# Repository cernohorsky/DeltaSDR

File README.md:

# DeltaSDR
HF Software Defined Radio Transceiver that includes ADC and DAC circuits. No soundcard is needed. Board communicates only trough one USB cable. Very good software support trough Hamlib. Ideal for digital modes such a FT8 on Raspberry Pi.

- 96kHz digital I/Q interface.
- more then 80dB dynamic range.
- DG8SAQ/PE0FKO/SoftRock control interface.
- Open Source firmware (https://github.com/AE9RB/peaberry)
- SWD/JTAG port.

ToDo:
- Change SMA and USB footprints
- Add PA
- Implement band switching

Based on: AE9RB Peaberry SDR and RS-HFIQ Transceiver

#sdr, #hf, #ham, #radio, #ft8, #wsjt-x, #shortwave, #usb

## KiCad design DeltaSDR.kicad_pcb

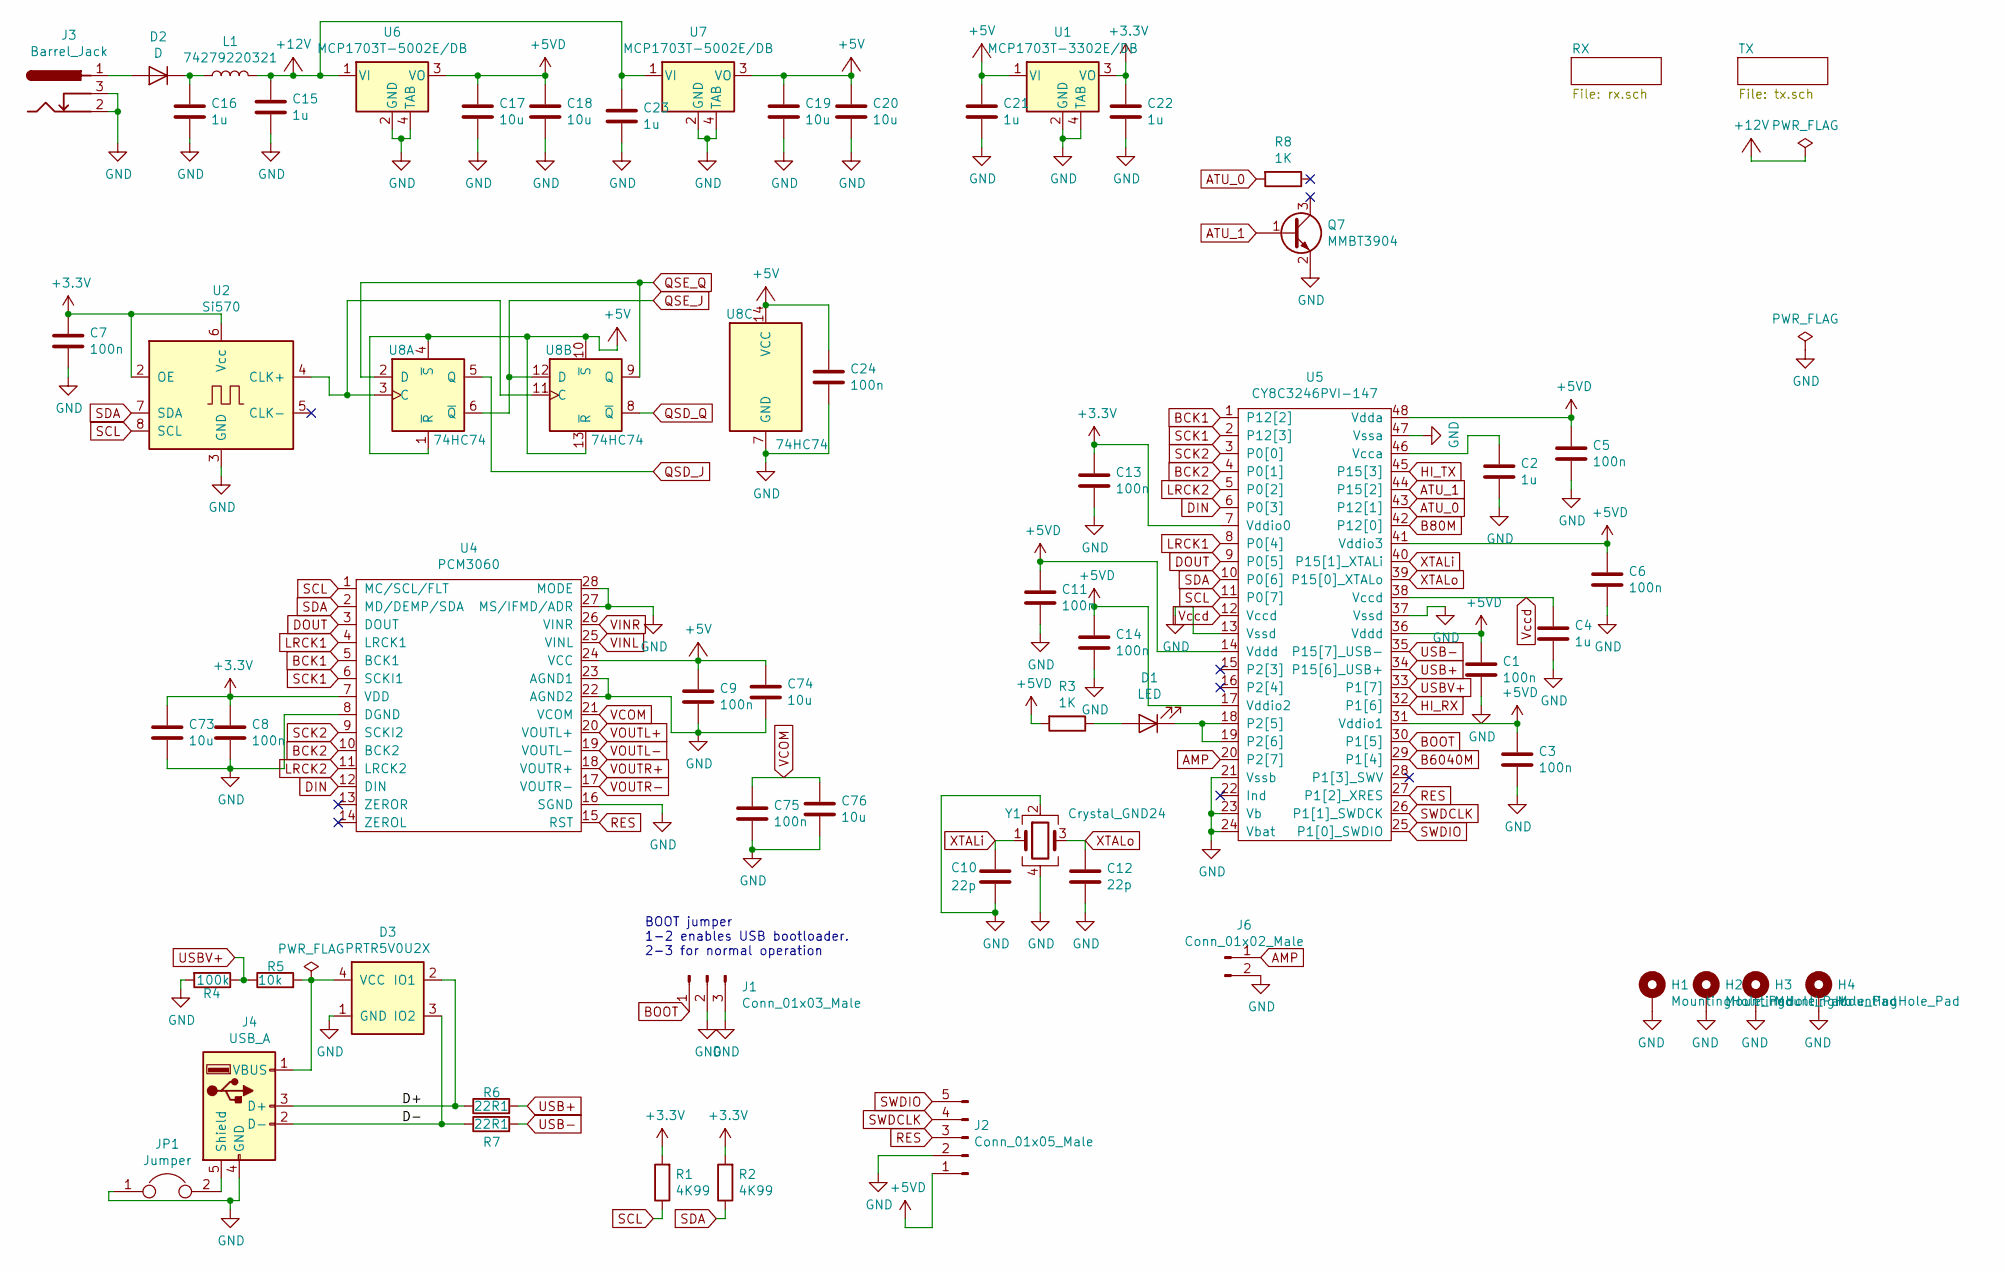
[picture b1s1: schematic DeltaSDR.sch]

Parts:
C1, C3, C5, C6, C7, C8, C9, C11, C13, C14, C24, C75: 100n; C_0603_1608Metric
C2, C4, C16, C21, C22: 1u; C_0603_1608Metric
C10, C12: 22p; C_0603_1608Metric
C15, C23: 1u; C_0805_2012Metric
C17, C18, C19, C20, C73, C74, C76: 10u; C_0805_2012Metric
D1: LED; LED_0805_2012Metric
D2: D; D_SMB
D3: PRTR5V0U2X; SOT-143
H1, H2, H3, H4: MountingHole_Pad; MountingHole_3.2mm_M3_Pad_Via
J1: Conn_01x03_Male; PinHeader_1x03_P2.54mm_Vertical
J2: Conn_01x05_Male; PinHeader_1x05_P2.54mm_Vertical
J3: Barrel_Jack; BarrelJack_Horizontal
J4: USB_A; USB_B_TE_5787834_Vertical
J6: Conn_01x02_Male; PinSocket_1x02_P2.54mm_Vertical_SMD_Pin1Right
JP1: Jumper; SolderJumper-2_P1.3mm_Open_RoundedPad1.0x1.5mm
L1: 74279220321; L_0805_2012Metric
Q7: MMBT3904; SOT-23
R1, R2: 4K99; R_0603_1608Metric
R3, R8: 1K; R_0603_1608Metric
R4: 100k; R_0603_1608Metric
R5: 10k; R_0603_1608Metric
R6, R7: 22R1; R_0603_1608Metric
U1: MCP1703T-3302E/DB; SOT-223
U2: Si570; Oscillator_SMD_SI570_SI571_Standard
U4: PCM3060; TSSOP-28_4.4x9.7mm_P0.65mm
U5: CY8C3246PVI-147; SSOP-48_7.5x15.9mm_P0.635mm
U6, U7: MCP1703T-5002E/DB; SOT-223
U8: 74HC74; SOIC-14_3.9x8.7mm_P1.27mm
Y1: Crystal_GND24; Crystal_SMD_3225-4Pin_3.2x2.5mm

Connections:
+3V3: C7.1, C8.1, C13.1, C22.1, C73.1, R1.2, R2.2, U1.3 (VO), U2.2 (OE), U2.6 (Vcc), U4.7 (VDD), U5.7 (Vddio0)
+5V: C9.1, C19.1, C20.1, C21.1, C24.1, C74.1, U1.1 (VI), U4.24 (VCC), U7.3 (VO), U8.1 (~R), U8.4 (~S), U8.10 (~S), U8.13 (~R), U8.14 (VCC); also elsewhere on the board
+5VD: C1.1, C3.1, C5.1, C6.1, C11.1, C14.1, C17.1, C18.1, J2.1, R3.2, U5.14 (Vddd), U5.17 (Vddio2), U5.31 (Vddio1), U5.36 (Vddd), U5.41 (Vddio3), U5.48 (Vdda), U6.3 (VO)
+12V: C15.1, C23.1, L1.2, U6.1 (VI), U7.1 (VI); also elsewhere on the board
/D+: D3.2 (IO1), J4.3 (D+), R6.1
/D-: D3.3 (IO2), J4.2 (D-), R7.1
AMP: J6.1, U5.20 (P2[7])
ATU_0: R8.2, U5.43 (P12[1])
ATU_1: Q7.1 (B), U5.44 (P15[2])
B80M: U5.42 (P12[0]); also elsewhere on the board
B6040M: U5.29 (P1[4]); also elsewhere on the board
BCK1: U4.5 (BCK1), U5.1 (P12[2])
BCK2: U4.10 (BCK2), U5.4 (P0[1])
BOOT: J1.1, U5.30 (P1[5])
DIN: U4.12 (DIN), U5.6 (P0[3])
DOUT: U4.3 (DOUT), U5.9 (P0[5])
GND: C1.2, C2.2, C3.2, C4.2, C5.2, C6.2, C7.2, C8.2, C9.2, C10.2, C11.2, C12.2, C13.2, C14.2, C15.2, C16.2, C17.2, C18.2, C19.2, C20.2, C21.2, C22.2, C23.2, C24.2, C73.2, C74.2, C75.2, C76.2, D3.1 (GND), H1.1, H2.1, H3.1, H4.1, J1.2, J1.3, J2.2, J3.2, J3.3, J4.4 (GND), J6.2, JP1.1, Q7.2 (E), R4.2, U1.2 (GND), U1.4 (TAB), U2.3 (GND), U4.8 (DGND), U4.16 (SGND), U4.22 (AGND2), U4.23 (AGND1), U4.27 (MS/IFMD/ADR), U4.28 (MODE), U5.13 (Vssd), U5.21 (Vssb), U5.23 (Vb), U5.24 (Vbat), U5.37 (Vssd), U5.47 (Vssa), U6.2 (GND), U6.4 (TAB), U7.2 (GND), U7.4 (TAB), U8.7 (GND), Y1.2, Y1.4; also elsewhere on the board
HI_RX: U5.32 (P1[6]); also elsewhere on the board
HI_TX: U5.45 (P15[3]); also elsewhere on the board
LRCK1: U4.4 (LRCK1), U5.8 (P0[4])
LRCK2: U4.11 (LRCK2), U5.5 (P0[2])
unnamed: C2.1, U5.46 (Vcca)
unnamed: C16.1, D2.1 (K), L1.1
unnamed: D1.1 (K), U5.18 (P2[5]), U5.19 (P2[6])
unnamed: D1.2 (A), R3.1
unnamed: D2.2 (A), J3.1
unnamed: D3.4 (VCC), J4.1 (VBUS), R5.2
unnamed: J4.5 (Shield), JP1.2
unnamed: U2.4 (CLK+), U8.3 (C), U8.11 (C)
QSD_J: U8.5 (Q); also elsewhere on the board
QSD_Q: U8.8 (~Q); also elsewhere on the board
QSE_J: U8.6 (~Q), U8.12 (D); also elsewhere on the board
QSE_Q: U8.2 (D), U8.9 (Q); also elsewhere on the board
RES: J2.3, U4.15 (RST), U5.27 (P1[2]_XRES)
SCK1: U4.6 (SCKI1), U5.2 (P12[3])
SCK2: U4.9 (SCKI2), U5.3 (P0[0])
SCL: R1.1, U2.8 (SCL), U4.1 (MC/SCL/FLT), U5.11 (P0[7])
SDA: R2.1, U2.7 (SDA), U4.2 (MD/DEMP/SDA), U5.10 (P0[6])
SWDCLK: J2.4, U5.26 (P1[1]_SWDCK)
SWDIO: J2.5, U5.25 (P1[0]_SWDIO)
USB+: R6.2, U5.34 (P15[6]_USB+)
USB-: R7.2, U5.35 (P15[7]_USB-)
USBV+: R4.1, R5.1, U5.33 (P1[7])
VCOM: C75.1, C76.1, U4.21 (VCOM); also elsewhere on the board
VINL: U4.25 (VINL); also elsewhere on the board
VINR: U4.26 (VINR); also elsewhere on the board
VOUTL+: U4.20 (VOUTL+); also elsewhere on the board
VOUTL-: U4.19 (VOUTL-); also elsewhere on the board
VOUTR+: U4.18 (VOUTR+); also elsewhere on the board
VOUTR-: U4.17 (VOUTR-); also elsewhere on the board
Vccd: C4.1, U5.12 (Vccd), U5.38 (Vccd)
XTALi: C10.1, U5.40 (P15[1]_XTALi), Y1.1
XTALo: C12.1, U5.39 (P15[0]_XTALo), Y1.3

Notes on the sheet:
BOOT jumper 1-2 enables USB bootloader. 2-3 for normal operation

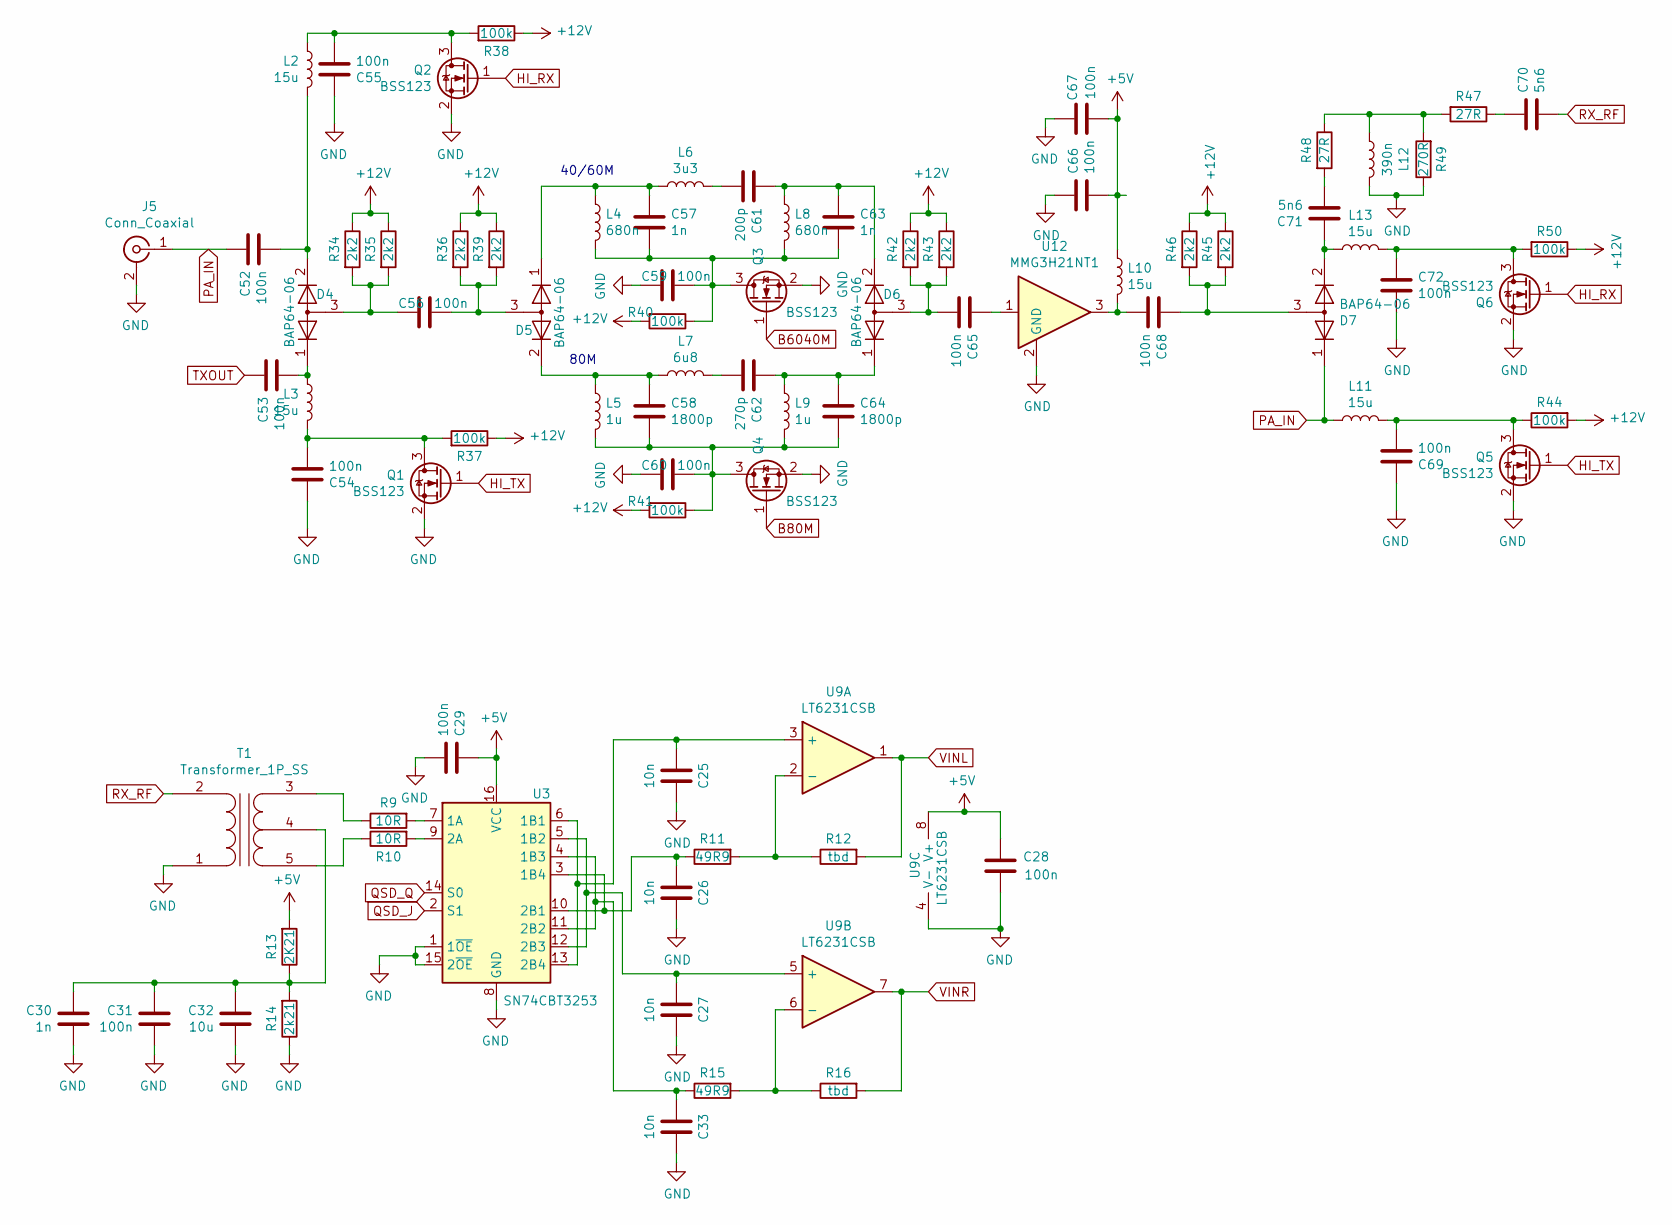
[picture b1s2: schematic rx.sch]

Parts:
C25, C26, C27, C33: 10n; C_0603_1608Metric
C28, C29, C31, C52, C53, C54, C55, C56, C59, C60, C65, C66, C67, C68, C69, C72: 100n; C_0603_1608Metric
C30, C57, C63: 1n; C_0603_1608Metric
C32: 10u; C_0805_2012Metric
C58, C64: 1800p; C_0603_1608Metric
C61: 200p; C_0603_1608Metric
C62: 270p; C_0603_1608Metric
C70, C71: 5n6; C_0603_1608Metric
D4, D5, D6, D7: BAP64-06; SOT-23
J5: Conn_Coaxial; SMA_Amphenol_132289_EdgeMount
L2, L3, L10, L11, L13: 15u; L_Taiyo-Yuden_NR-30xx_HandSoldering
L4, L8: 680n; L_Abracon_ASPI-3012S
L5, L9: 1u; L_Abracon_ASPI-3012S
L6: 3u3; L_Abracon_ASPI-3012S
L7: 6u8; L_Abracon_ASPI-3012S
L12: 390n; L_0805_2012Metric
Q1, Q2, Q3, Q4, Q5, Q6: BSS123; SOT-23
R9, R10: 10R; R_0603_1608Metric
R11, R15: 49R9; R_0603_1608Metric
R12, R16: tbd; R_0603_1608Metric
R13: 2K21; R_0603_1608Metric
R14: 2k21; R_0603_1608Metric
R34, R35, R36, R39, R42, R43, R45, R46: 2k2; R_0603_1608Metric
R37, R38, R40, R41, R44, R50: 100k; R_0603_1608Metric
R47, R48: 27R; R_0603_1608Metric
R49: 270R; R_0603_1608Metric
T1: Transformer_1P_SS; Transformer_MACOM_SM-22
U3: SN74CBT3253; SOIC-16_3.9x9.9mm_P1.27mm
U9: LT6231CSB; SOIC-8_3.9x4.9mm_P1.27mm
U12: MMG3H21NT1; SOT-89-3

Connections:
+5V: C28.1, C29.1, C66.2, C67.2, L10.1, R13.2, U3.16 (VCC), U9.8 (V+); also elsewhere on the board
+12V: R34.1, R35.1, R36.1, R37.1, R38.1, R39.1, R40.2, R41.2, R42.1, R43.1, R44.2, R45.1, R46.1, R50.1; also elsewhere on the board
B80M: Q4.1 (G); also elsewhere on the board
B6040M: Q3.1 (G); also elsewhere on the board
GND: C25.1, C26.1, C27.1, C28.2, C29.2, C30.2, C31.2, C32.2, C33.1, C54.1, C55.1, C59.2, C60.2, C66.1, C67.1, C69.1, C72.2, J5.2 (Ext), L12.2, Q1.2 (S), Q2.2 (S), Q3.2 (S), Q4.2 (S), Q5.2 (S), Q6.2 (S), R14.1, R49.1, T1.1 (AA), U3.1 (1~OE), U3.8 (GND), U3.15 (2~OE), U9.4 (V-), U12.2 (GND); also elsewhere on the board
HI_RX: Q2.1 (G), Q6.1 (G); also elsewhere on the board
HI_TX: Q1.1 (G), Q5.1 (G); also elsewhere on the board
unnamed: C25.2, U3.6 (1B1), U3.13 (2B4), U9.3 (+)
unnamed: C26.2, R11.1, U3.3 (1B4), U3.10 (2B1)
unnamed: C27.2, U3.5 (1B2), U3.12 (2B3), U9.5 (+)
unnamed: C30.1, C31.1, C32.1, R13.1, R14.2, T1.4 (SC)
unnamed: C33.2, R15.1, U3.4 (1B3), U3.11 (2B2)
unnamed: C52.2, D4.2 (K), L2.1
unnamed: C53.2, D4.1 (K), L3.2
unnamed: C54.2, L3.1, Q1.3 (D), R37.2
unnamed: C55.2, L2.2, Q2.3 (D), R38.2
unnamed: C56.1, D5.3 (A), R36.2, R39.2
unnamed: C56.2, D4.3 (A), R34.2, R35.2
unnamed: C57.1, D5.1 (K), L4.1, L6.1
unnamed: C57.2, C59.1, C63.2, L4.2, L8.2, Q3.3 (D), R40.1
unnamed: C58.1, D5.2 (K), L5.1, L7.1
unnamed: C58.2, C60.1, C64.2, L5.2, L9.2, Q4.3 (D), R41.1
unnamed: C61.1, C63.1, D6.2 (K), L8.1
unnamed: C61.2, L6.2
unnamed: C62.1, C64.1, D6.1 (K), L9.1
unnamed: C62.2, L7.2
unnamed: C65.1, U12.1
unnamed: C65.2, D6.3 (A), R42.2, R43.2
unnamed: C68.1, D7.3 (A), R45.2, R46.2
unnamed: C68.2, L10.2, U12.3
unnamed: C69.2, L11.1, Q5.3 (D), R44.1
unnamed: C70.1, R47.1
unnamed: C71.1, D7.2 (K), L13.1
unnamed: C71.2, R48.2
unnamed: C72.1, L13.2, Q6.3 (D), R50.2
unnamed: L12.1, R47.2, R48.1, R49.2
unnamed: R9.1, T1.3 (SA)
unnamed: R9.2, U3.7 (1A)
unnamed: R10.1, T1.5 (SB)
unnamed: R10.2, U3.9 (2A)
unnamed: R11.2, R12.1, U9.2 (-)
unnamed: R15.2, R16.1, U9.6 (-)
PA_IN: C52.1, D7.1 (K), J5.1 (In), L11.2
QSD_J: U3.2 (S1); also elsewhere on the board
QSD_Q: U3.14 (S0); also elsewhere on the board
RX_RF: C70.2, T1.2 (AB)
TXOUT: C53.1; also elsewhere on the board
VINL: R12.2, U9.1; also elsewhere on the board
VINR: R16.2, U9.7; also elsewhere on the board

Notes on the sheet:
80M
40/60M

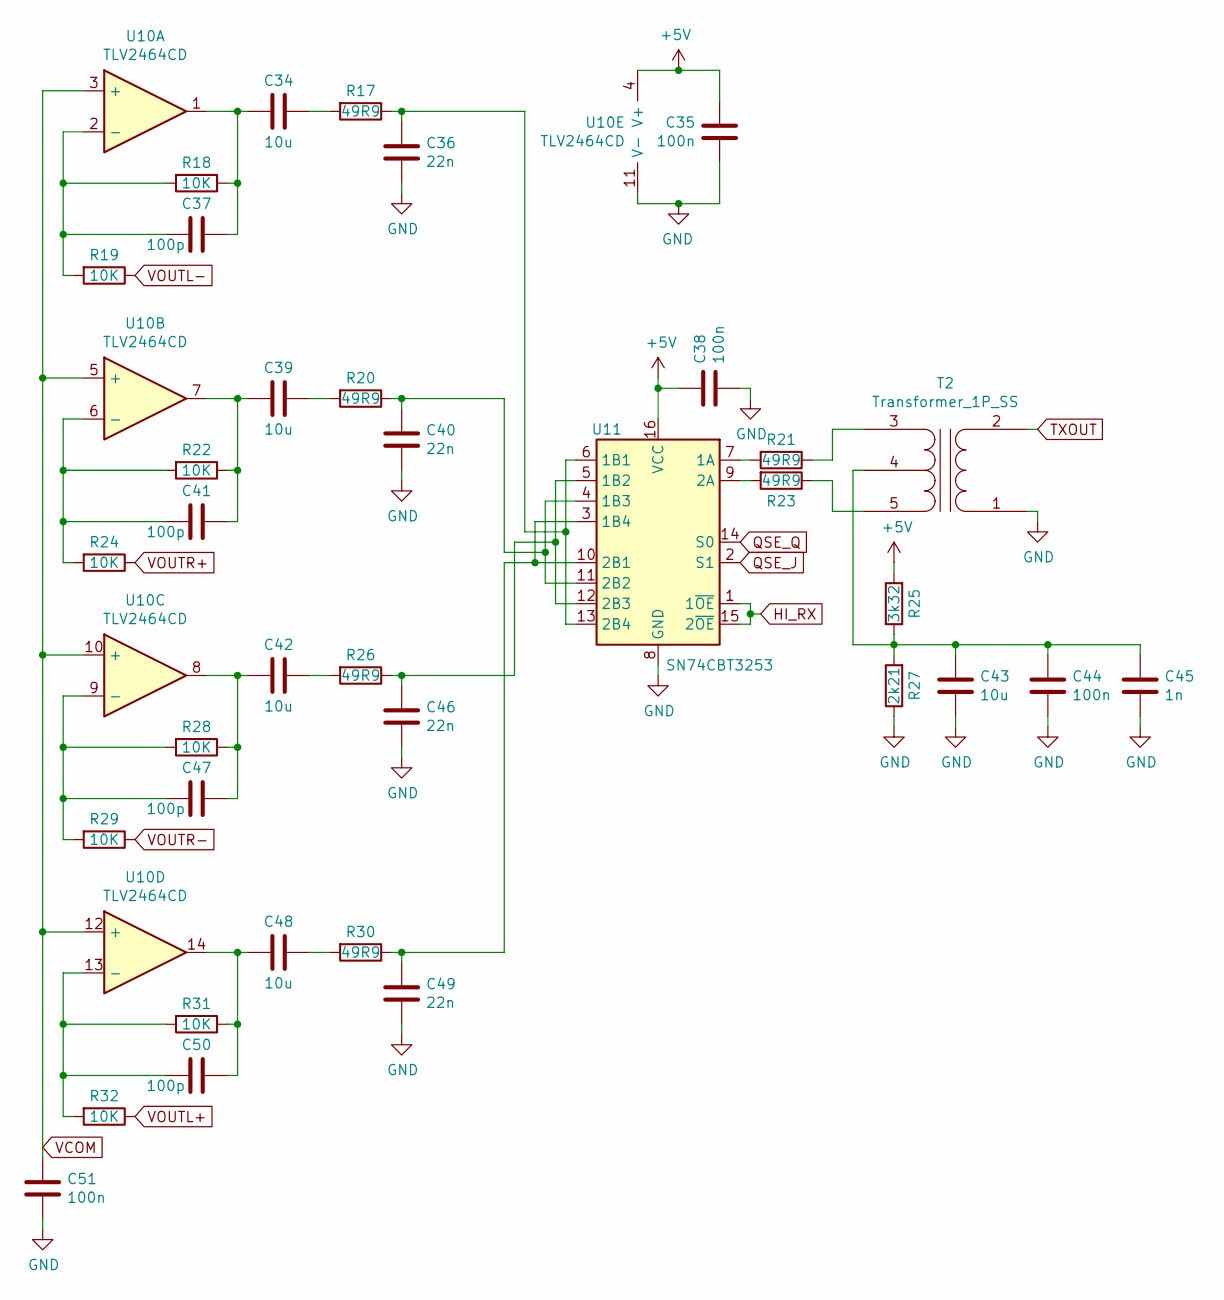
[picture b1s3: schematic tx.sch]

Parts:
C34, C39, C42, C43, C48: 10u; C_0805_2012Metric
C35, C38, C44, C51: 100n; C_0603_1608Metric
C36, C40, C46, C49: 22n; C_0603_1608Metric
C37, C41, C47, C50: 100p; C_0603_1608Metric
C45: 1n; C_0603_1608Metric
R17, R20, R21, R23, R26, R30: 49R9; R_0603_1608Metric
R18, R19, R22, R24, R28, R29, R31, R32: 10K; R_0603_1608Metric
R25: 3k32; R_0603_1608Metric
R27: 2k21; R_0603_1608Metric
T2: Transformer_1P_SS; Transformer_MACOM_SM-22
U10: TLV2464CD; SOIC-14_3.9x8.7mm_P1.27mm
U11: SN74CBT3253; SOIC-16_3.9x9.9mm_P1.27mm

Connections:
+5V: C35.1, C38.1, R25.2, U10.4 (V+), U11.16 (VCC); also elsewhere on the board
GND: C35.2, C36.2, C38.2, C40.2, C43.2, C44.2, C45.2, C46.2, C49.2, C51.2, R27.1, T2.1 (AA), U10.11 (V-), U11.8 (GND); also elsewhere on the board
HI_RX: U11.1 (1~OE), U11.15 (2~OE); also elsewhere on the board
unnamed: C34.1, R17.2
unnamed: C34.2, C37.1, R18.1, U10.1
unnamed: C36.1, R17.1, U11.6 (1B1), U11.13 (2B4)
unnamed: C37.2, R18.2, R19.2, U10.2 (-)
unnamed: C39.1, R20.2
unnamed: C39.2, C41.1, R22.1, U10.7
unnamed: C40.1, R20.1, U11.4 (1B3), U11.11 (2B2)
unnamed: C41.2, R22.2, R24.2, U10.6 (-)
unnamed: C42.1, R26.2
unnamed: C42.2, C47.1, R28.1, U10.8
unnamed: C43.1, C44.1, C45.1, R25.1, R27.2, T2.4 (SC)
unnamed: C46.1, R26.1, U11.5 (1B2), U11.12 (2B3)
unnamed: C47.2, R28.2, R29.2, U10.9 (-)
unnamed: C48.1, R30.2
unnamed: C48.2, C50.1, R31.1, U10.14
unnamed: C49.1, R30.1, U11.3 (1B4), U11.10 (2B1)
unnamed: C50.2, R31.2, R32.2, U10.13 (-)
unnamed: R21.2, U11.7 (1A)
unnamed: R23.2, U11.9 (2A)
QSE_J: U11.2 (S1); also elsewhere on the board
QSE_Q: U11.14 (S0); also elsewhere on the board
TXOUT: T2.2 (AB); also elsewhere on the board
VCOM: C51.1, U10.3 (+), U10.5 (+), U10.10 (+), U10.12 (+); also elsewhere on the board
VOUTL+: R32.1; also elsewhere on the board
VOUTL-: R19.1; also elsewhere on the board
VOUTR+: R24.1; also elsewhere on the board
VOUTR-: R29.1; also elsewhere on the board

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
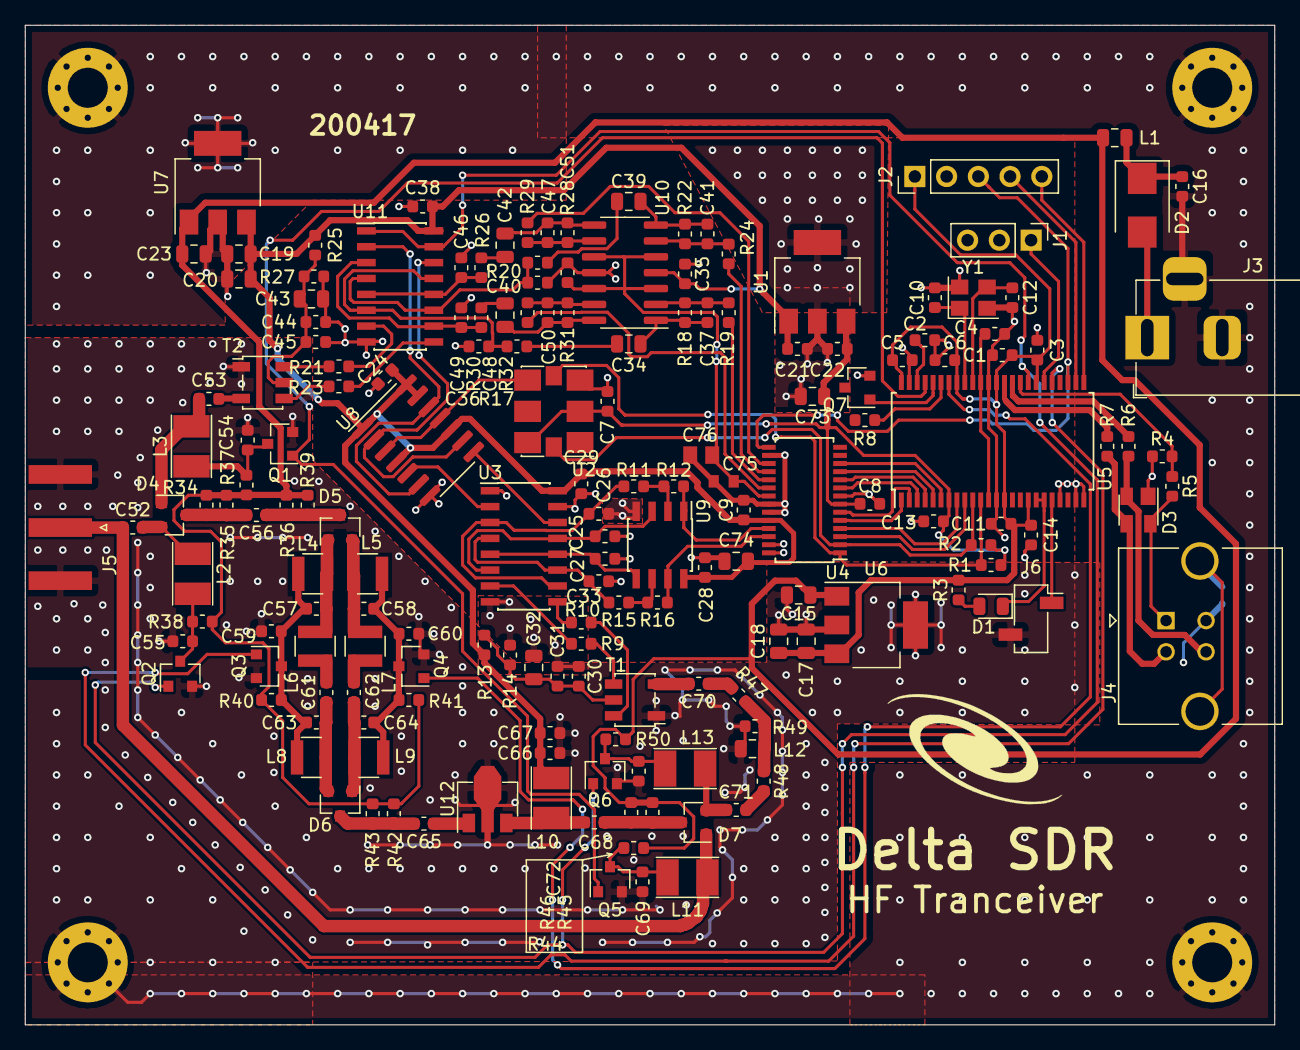
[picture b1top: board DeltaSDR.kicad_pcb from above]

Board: 2 copper layers, 100.0 x 80.0 mm, 178 parts (1 on the bottom side), 112 nets.

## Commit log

2020-04-07 Schemtic: MCU, Codec, Basic RX and TX
2020-04-08 Added: D Flip-Flip, LDOs, USB
2020-04-09 Added RF front end and LNA
2020-04-10 First layouting
2020-04-11 Layout: All components connected
2020-04-11 Changed RF front end layout
2020-04-12 Added remaining switching signals and polygons
2020-04-12 Changed board size, changed PA_IN signal position, changed LDOs, added 50 ohm tracks andvias
2020-04-13 Changed connectors position, ground separation, added lot of vias
2020-04-13 Improved ground separation and silk screen
2020-04-13 ERC, DRC done, added output for ATU and AMP
2020-04-14 Changed LO position and OPAMPs wiring
2020-04-16 PCM3060 suplied from different voltage rail. Improved ground separation and USB layout
2020-04-17 Release. Generated gerbers and BOM
2020-04-17 Data sended to menufacturer
2020-08-24 Add files via upload
    Added pictures
2020-08-25 Corrected Q6 connection, RX schematic clean up
2020-08-25 Changed mixers footprints, added 3D models, silk screen correction
2020-08-25 Improved band pass filter layout
2020-08-25 Changed layout of LT6231, changed RX transformer caps ground.
2020-08-26 Improved layout of band pass switches, edited README.md
2020-08-26 Added latest FW, Win USB driver and references
2020-08-28 Changed LDOs
2020-08-31 Wrong TX resistors values correction.
2020-09-11 Corrected wrong TX opamp capacitors values
2020-09-11 TX opamp improved layout.
2020-09-11 Added capacitors to codec's VCOM
2020-09-16 Minor SilkScreen layer improvement
2020-09-19 A lot of minor layout changes
2020-09-21 TX sample caps closer to MUX, changed SI570 orientation
2020-09-21 Revert "Data sended to menufacturer"
    This reverts commit 1a5cfaeb8aaaa6af1e1a28fc99f5d1e33d3756e5.
2020-09-22 Added TX spectrum measurement
